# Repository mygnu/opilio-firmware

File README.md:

# opilio-firmware

Firmware for STM32F103C8 based custom board for PC water-cooling project.

Counterparts: 
- Linux TUI app can be found [here](https://github.com/mygnu/opilio)
- PCB Files [here](https://github.com/mygnu/opilio-pcb)

## Flashing an opilio board
- install rust from [rustup](https://rustup.rs)
- `cargo install probe-run cargo-flash flip-link`
- `git clone https://github.com/mygnu/opilio`
- `git clone https://github.com/mygnu/opilio-firmware`
- `cd opilio-firmware && cargo flash --chip STM32F103C8 --release`

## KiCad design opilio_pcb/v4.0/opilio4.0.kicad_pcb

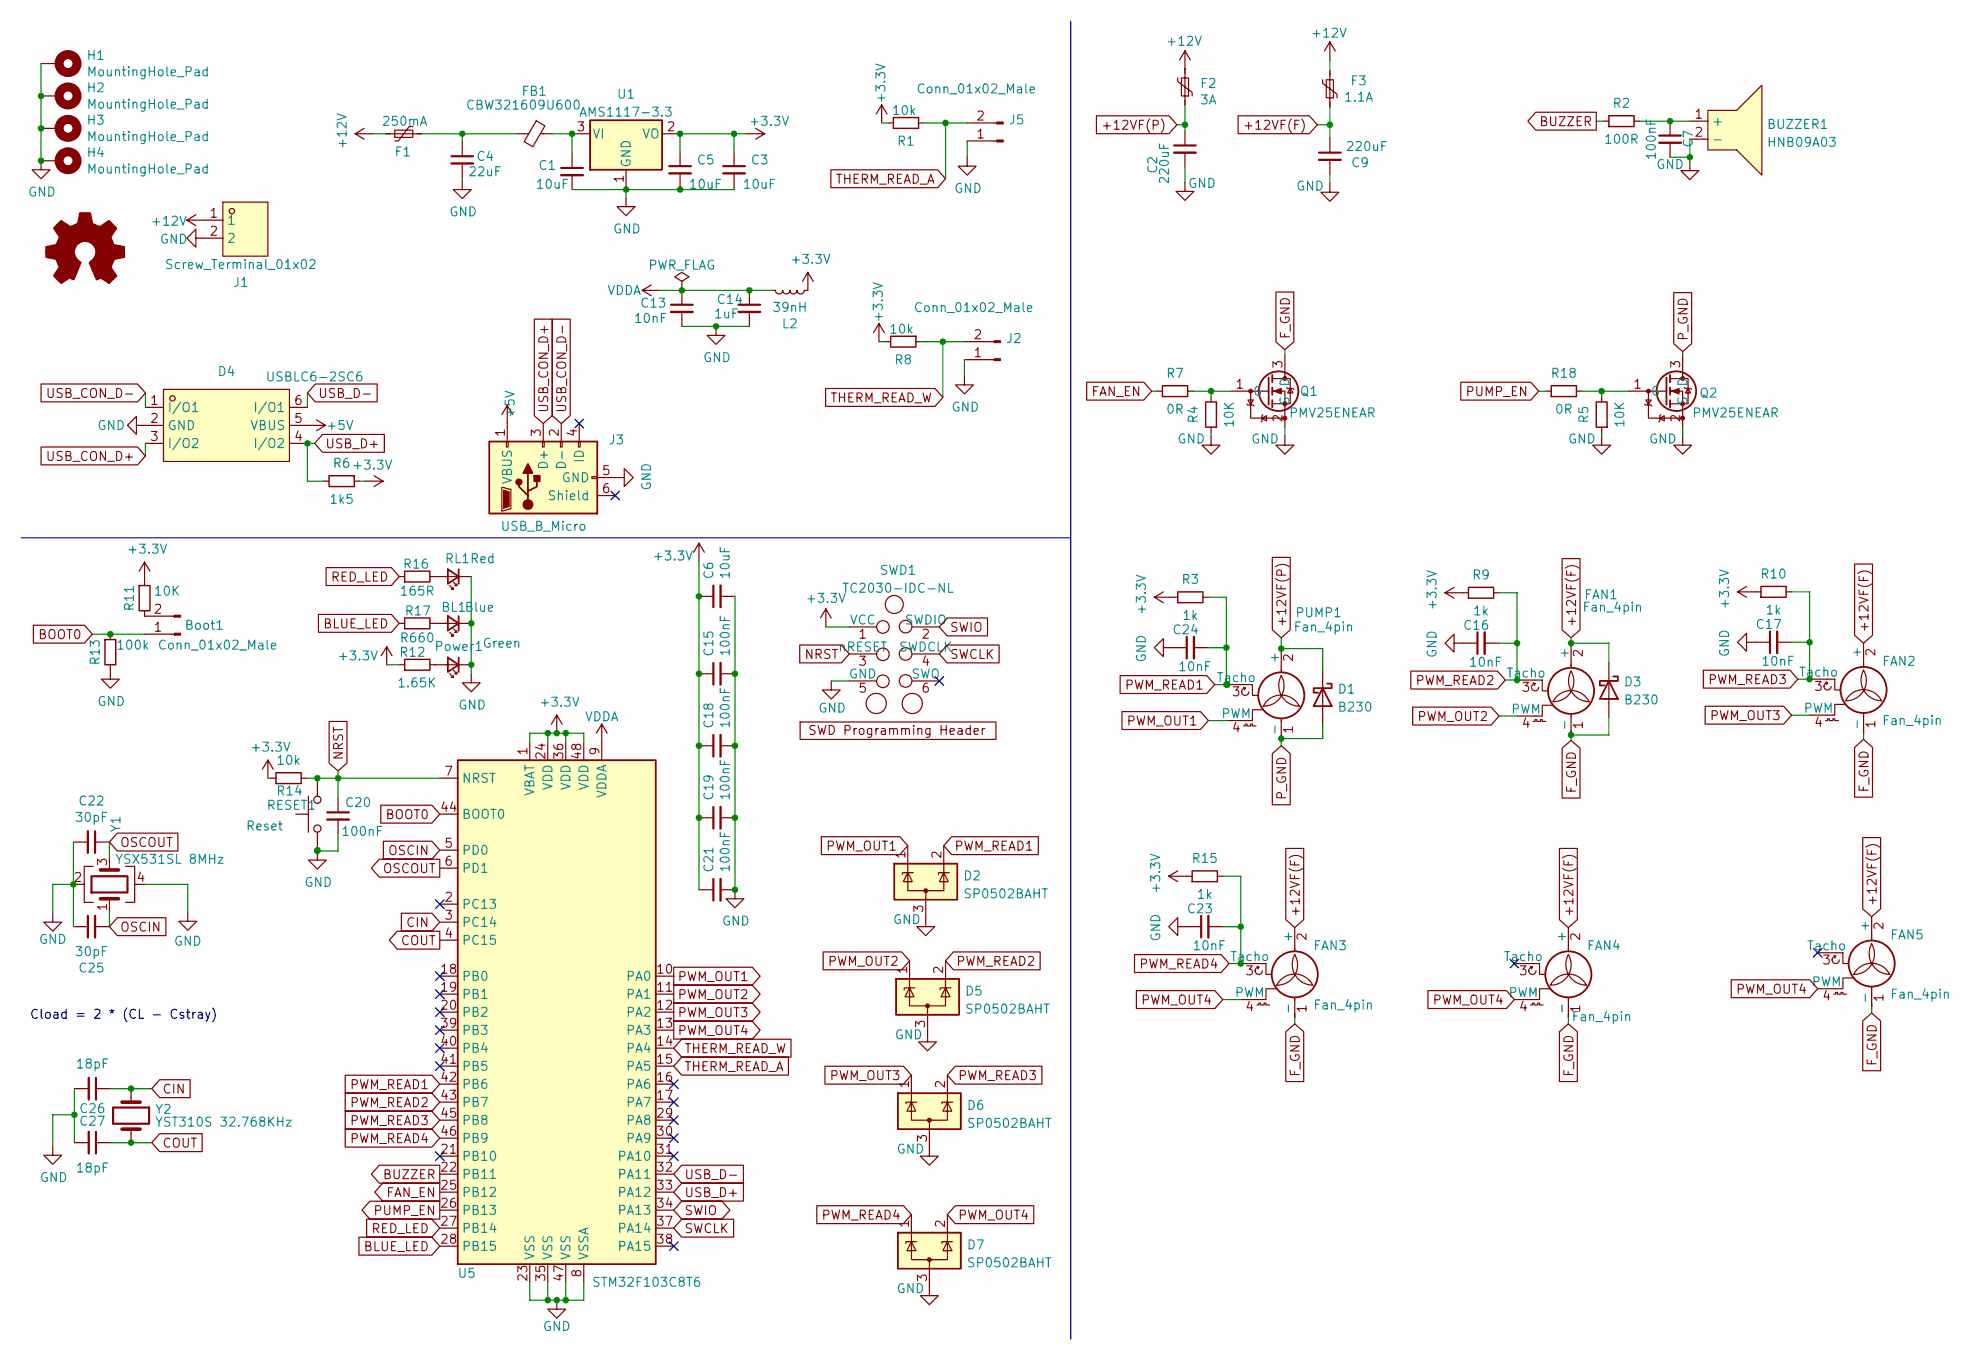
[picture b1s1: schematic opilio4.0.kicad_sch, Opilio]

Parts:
BL1: Blue; LED_0603_1608Metric_Pad1.05x0.95mm_HandSolder
BUZZER1: HNB09A03; BUZ-TH_BD9.0-P5.00-D0.6-FD; LCSC Part C96102
Boot1: Conn_01x02_Male; PinHeader_1x02_P2.54mm_Vertical
C1, C3, C5, C6: 10uF; C_0603_1608Metric_Pad1.08x0.95mm_HandSolder
C2, C9: 220uF; CP_Elec_6.3x7.7
C4: 22uF; C_1206_3216Metric_Pad1.33x1.80mm_HandSolder
C7, C15, C18, C19, C20, C21: 100nF; C_0603_1608Metric_Pad1.08x0.95mm_HandSolder
C13, C16, C17, C23, C24: 10nF; C_0603_1608Metric_Pad1.08x0.95mm_HandSolder
C14: 1uF; C_0603_1608Metric_Pad1.08x0.95mm_HandSolder
C22, C25: 30pF; C_0603_1608Metric_Pad1.08x0.95mm_HandSolder
C26, C27: 18pF; C_0603_1608Metric_Pad1.08x0.95mm_HandSolder
D1, D3: B230; D_SMB
D2, D5, D6, D7: SP0502BAHT; SOT-23
D4: USBLC6-2SC6; SOT-666-6_L1.6-W1.2-P0.50-LS1.6-BL; LCSC Part C2827693
F1: 250mA; Fuse_1206_3216Metric_Pad1.42x1.75mm_HandSolder
F2: 3A; Fuse_1812_4532Metric_Pad1.30x3.40mm_HandSolder
F3: 1.1A; Fuse_1206_3216Metric_Pad1.42x1.75mm_HandSolder
FAN1, FAN2, FAN3, FAN4, FAN5: Fan_4pin; FanPinHeader_1x04_P2.54mm_Vertical_no_hole
FB1: CBW321609U600; C_1206_3216Metric_Pad1.33x1.80mm_HandSolder
H1, H2, H3, H4: MountingHole_Pad; MountingHole_3mm_Pad_Via
J1: Screw_Terminal_01x02; CONN-TH_2P-P2.54_JL300-50002U01; LCSC Part C387831
J2, J5: Conn_01x02_Male; PinHeader_1x02_P2.54mm_Vertical
J3: USB_B_Micro; USB_Micro-B_Wuerth_629105150521_narrow_holes
L2: 39nH; L_0805_2012Metric_Pad1.05x1.20mm_HandSolder
LOGO1: Logo_Open_Hardware_Small; OSHW-Logo2_9.8x8mm_SilkScreen
PUMP1: Fan_4pin; FanPinHeader_1x04_P2.54mm_Vertical_no_hole
Power1: Green; LED_0603_1608Metric_Pad1.05x0.95mm_HandSolder
Q1, Q2: PMV25ENEAR; SOT-23_L2.9-W1.3-P1.90-LS2.4-BR; LCSC Part C458158
R1, R8, R14: 10k; R_0603_1608Metric_Pad0.98x0.95mm_HandSolder
R2: 100R; R_0603_1608Metric_Pad0.98x0.95mm_HandSolder
R3, R9, R10, R15: 1k; R_0603_1608Metric_Pad0.98x0.95mm_HandSolder
R4, R5, R11: 10K; R_0603_1608Metric_Pad0.98x0.95mm_HandSolder
R6: 1k5; R_0603_1608Metric_Pad0.98x0.95mm_HandSolder
R7, R18: 0R; R_0603_1608Metric_Pad0.98x0.95mm_HandSolder
R12: 1.65K; R_0603_1608Metric_Pad0.98x0.95mm_HandSolder
R13: 100k; R_0603_1608Metric_Pad0.98x0.95mm_HandSolder
R16: 165R; R_0603_1608Metric_Pad0.98x0.95mm_HandSolder
R17: R660; R_0603_1608Metric_Pad0.98x0.95mm_HandSolder
RESET1: Reset; SW-SMD_L6.0-W3.3-LS8.0
RL1: Red; LED_0603_1608Metric_Pad1.05x0.95mm_HandSolder
SWD1: TC2030-IDC-NL_SWD; Tag-Connect_TC2030-IDC-NL_2x03_P1.27mm_Vertical
U1: AMS1117-3.3; SOT-223-3_TabPin2
U5: STM32F103C8T6; LQFP-48_7x7mm_P0.5mm
Y1: YSX531SL 8MHz; Crystal_SMD_3225-4Pin_3.2x2.5mm
Y2: YST310S 32.768KHz; Crystal_SMD_3215-2Pin_3.2x1.5mm

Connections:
+3.3V: C3.1, C5.1, C6.1, C15.1, C18.1, C19.1, C21.1, L2.1, R1.2, R3.1, R6.1, R8.2, R9.1, R10.1, R11.1, R12.1, R14.1, R15.1, SWD1.1 (VCC), U1.2 (VO), U5.1 (VBAT), U5.24 (VDD), U5.36 (VDD), U5.48 (VDD)
+5V: D4.5 (VBUS), J3.1 (VBUS)
+12V: F1.1, F2.2, F3.2, J1.1
+12VF(F): C9.1, D3.1 (K), F3.1, FAN1.2 (+), FAN2.2 (+), FAN3.2 (+), FAN4.2 (+), FAN5.2 (+)
+12VF(P): C2.1, D1.1 (K), F2.1, PUMP1.2 (+)
BLUE_LED: R17.1, U5.28 (PB15)
BOOT0: Boot1.1, R13.1, U5.44 (BOOT0)
BUZZER: R2.1, U5.22 (PB11)
CIN: C26.1, U5.3 (PC14), Y2.1
COUT: C27.1, U5.4 (PC15), Y2.2
FAN_EN: R7.1, U5.25 (PB12)
F_GND: D3.2 (A), FAN1.1 (-), FAN2.1 (-), FAN3.1 (-), FAN4.1 (-), FAN5.1 (-), Q1.3 (D)
GND: BL1.1 (K), BUZZER1.2 (-), C1.2, C2.2, C3.2, C4.2, C5.2, C6.2, C7.2, C9.2, C13.2, C14.2, C15.2, C16.1, C17.1, C18.2, C19.2, C20.2, C21.2, C22.2, C23.1, C24.1, C25.1, C26.2, C27.2, D2.3 (A), D4.2 (GND), D5.3 (A), D6.3 (A), D7.3 (A), H1.1, H2.1, H3.1, H4.1, J1.2, J2.1, J3.5 (GND), J5.1, Power1.1 (K), Q1.2 (S), Q2.2 (S), R4.1, R5.1, R13.2, RESET1.1, RL1.1 (K), SWD1.5 (GND), U1.1 (GND), U5.8 (VSSA), U5.23 (VSS), U5.35 (VSS), U5.47 (VSS), Y1.2, Y1.4
NRST: C20.1, R14.2, RESET1.2, SWD1.3 (nRESET), U5.7 (NRST)
unnamed: BL1.2 (A), R17.2
unnamed: BUZZER1.1 (+), C7.1, R2.2
unnamed: Boot1.2, R11.2
unnamed: C1.1, FB1.1, U1.3 (VI)
unnamed: C4.1, F1.2, FB1.2
unnamed: Power1.2 (A), R12.2
unnamed: Q1.1 (G), R4.2, R7.2
unnamed: Q2.1 (G), R5.2, R18.2
unnamed: R16.2, RL1.2 (A)
OSCIN: C25.2, U5.5 (PD0), Y1.1
OSCOUT: C22.1, U5.6 (PD1), Y1.3
PUMP_EN: R18.1, U5.26 (PB13)
PWM_OUT1: D2.1 (K), PUMP1.4 (PWM), U5.10 (PA0)
PWM_OUT2: D5.1 (K), FAN1.4 (PWM), U5.11 (PA1)
PWM_OUT3: D6.1 (K), FAN2.4 (PWM), U5.12 (PA2)
PWM_OUT4: D7.2 (K), FAN3.4 (PWM), FAN4.4 (PWM), FAN5.4 (PWM), U5.13 (PA3)
PWM_READ1: C24.2, D2.2 (K), PUMP1.3 (Tacho), R3.2, U5.42 (PB6)
PWM_READ2: C16.2, D5.2 (K), FAN1.3 (Tacho), R9.2, U5.43 (PB7)
PWM_READ3: C17.2, D6.2 (K), FAN2.3 (Tacho), R10.2, U5.45 (PB8)
PWM_READ4: C23.2, D7.1 (K), FAN3.3 (Tacho), R15.2, U5.46 (PB9)
P_GND: D1.2 (A), PUMP1.1 (-), Q2.3 (D)
RED_LED: R16.1, U5.27 (PB14)
SWCLK: SWD1.4 (SWDCLK), U5.37 (PA14)
SWIO: SWD1.2 (SWDIO), U5.34 (PA13)
THERM_READ_A: J5.2, R1.1, U5.15 (PA5)
THERM_READ_W: J2.2, R8.1, U5.14 (PA4)
USB_CON_D+: D4.3 (I/O2), J3.3 (D+)
USB_CON_D-: D4.1 (I/O1), J3.2 (D-)
USB_D+: D4.4 (I/O2), R6.2, U5.33 (PA12)
USB_D-: D4.6 (I/O1), U5.32 (PA11)
VDDA: C13.1, C14.1, L2.2, U5.9 (VDDA)

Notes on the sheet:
Cload = 2 * (CL - Cstray)

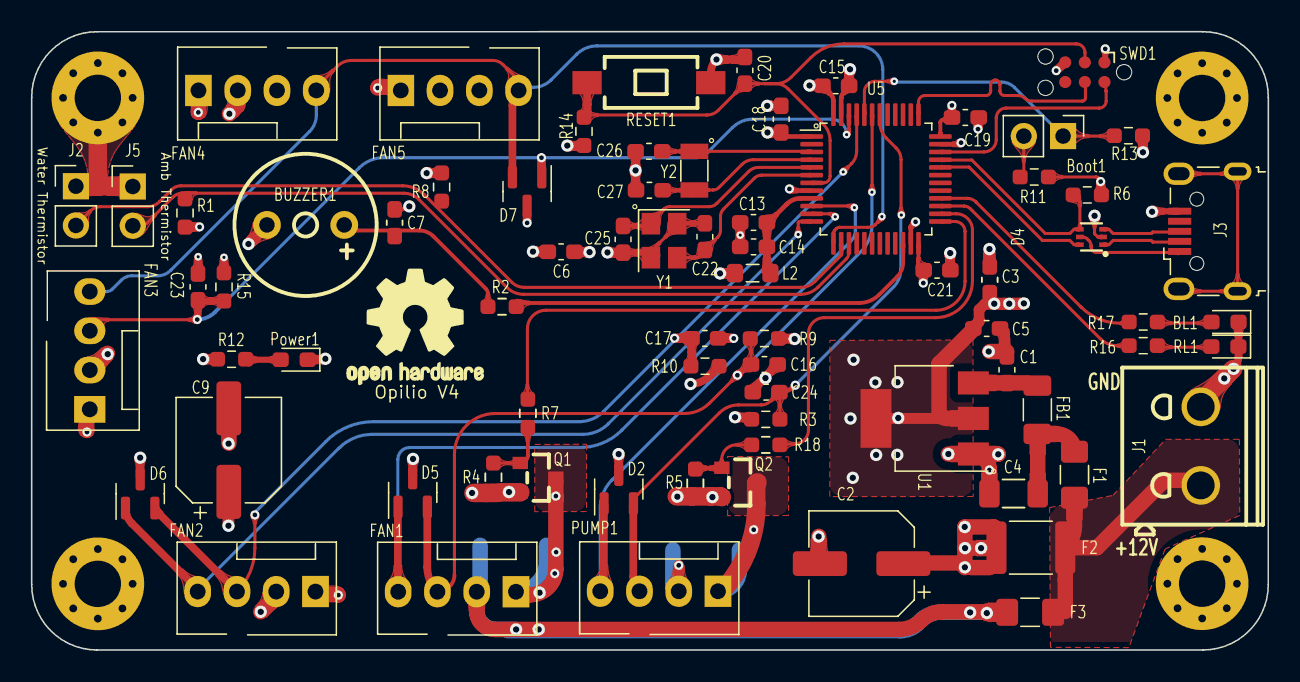
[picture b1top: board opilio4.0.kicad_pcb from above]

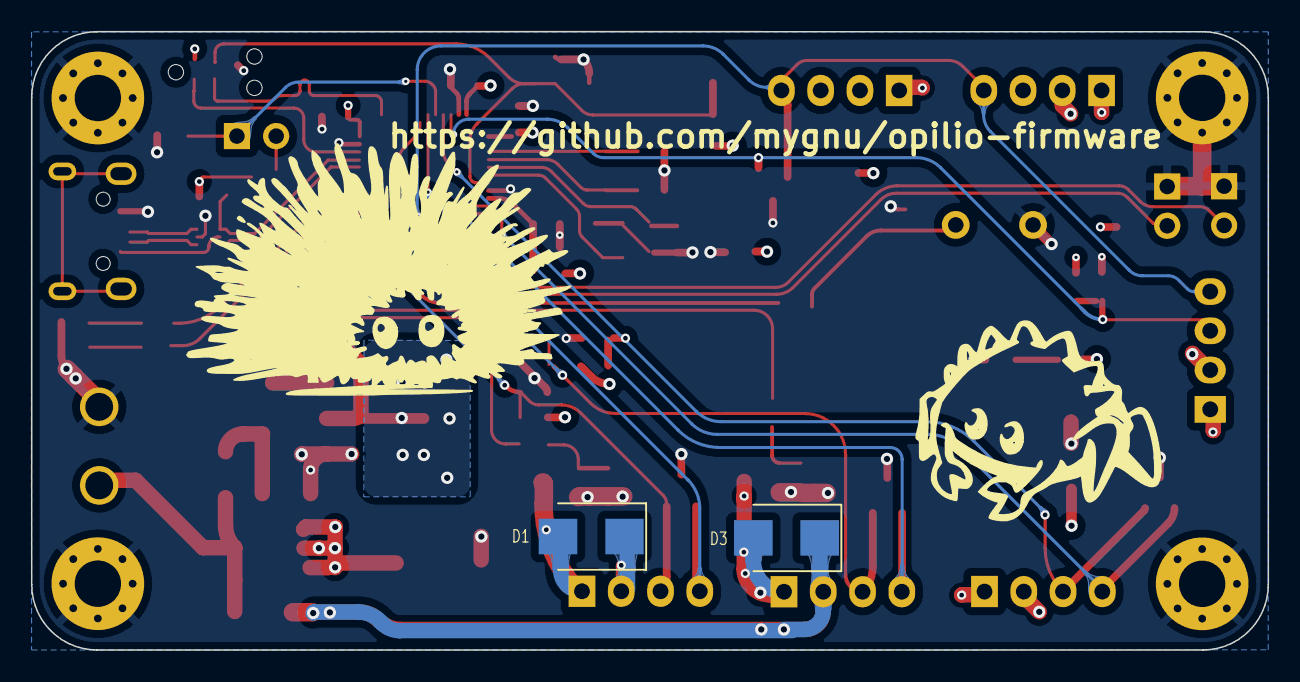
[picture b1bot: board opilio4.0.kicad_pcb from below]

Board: 4 copper layers, 80.0 x 40.0 mm, 81 parts (2 on the bottom side), 45 nets.

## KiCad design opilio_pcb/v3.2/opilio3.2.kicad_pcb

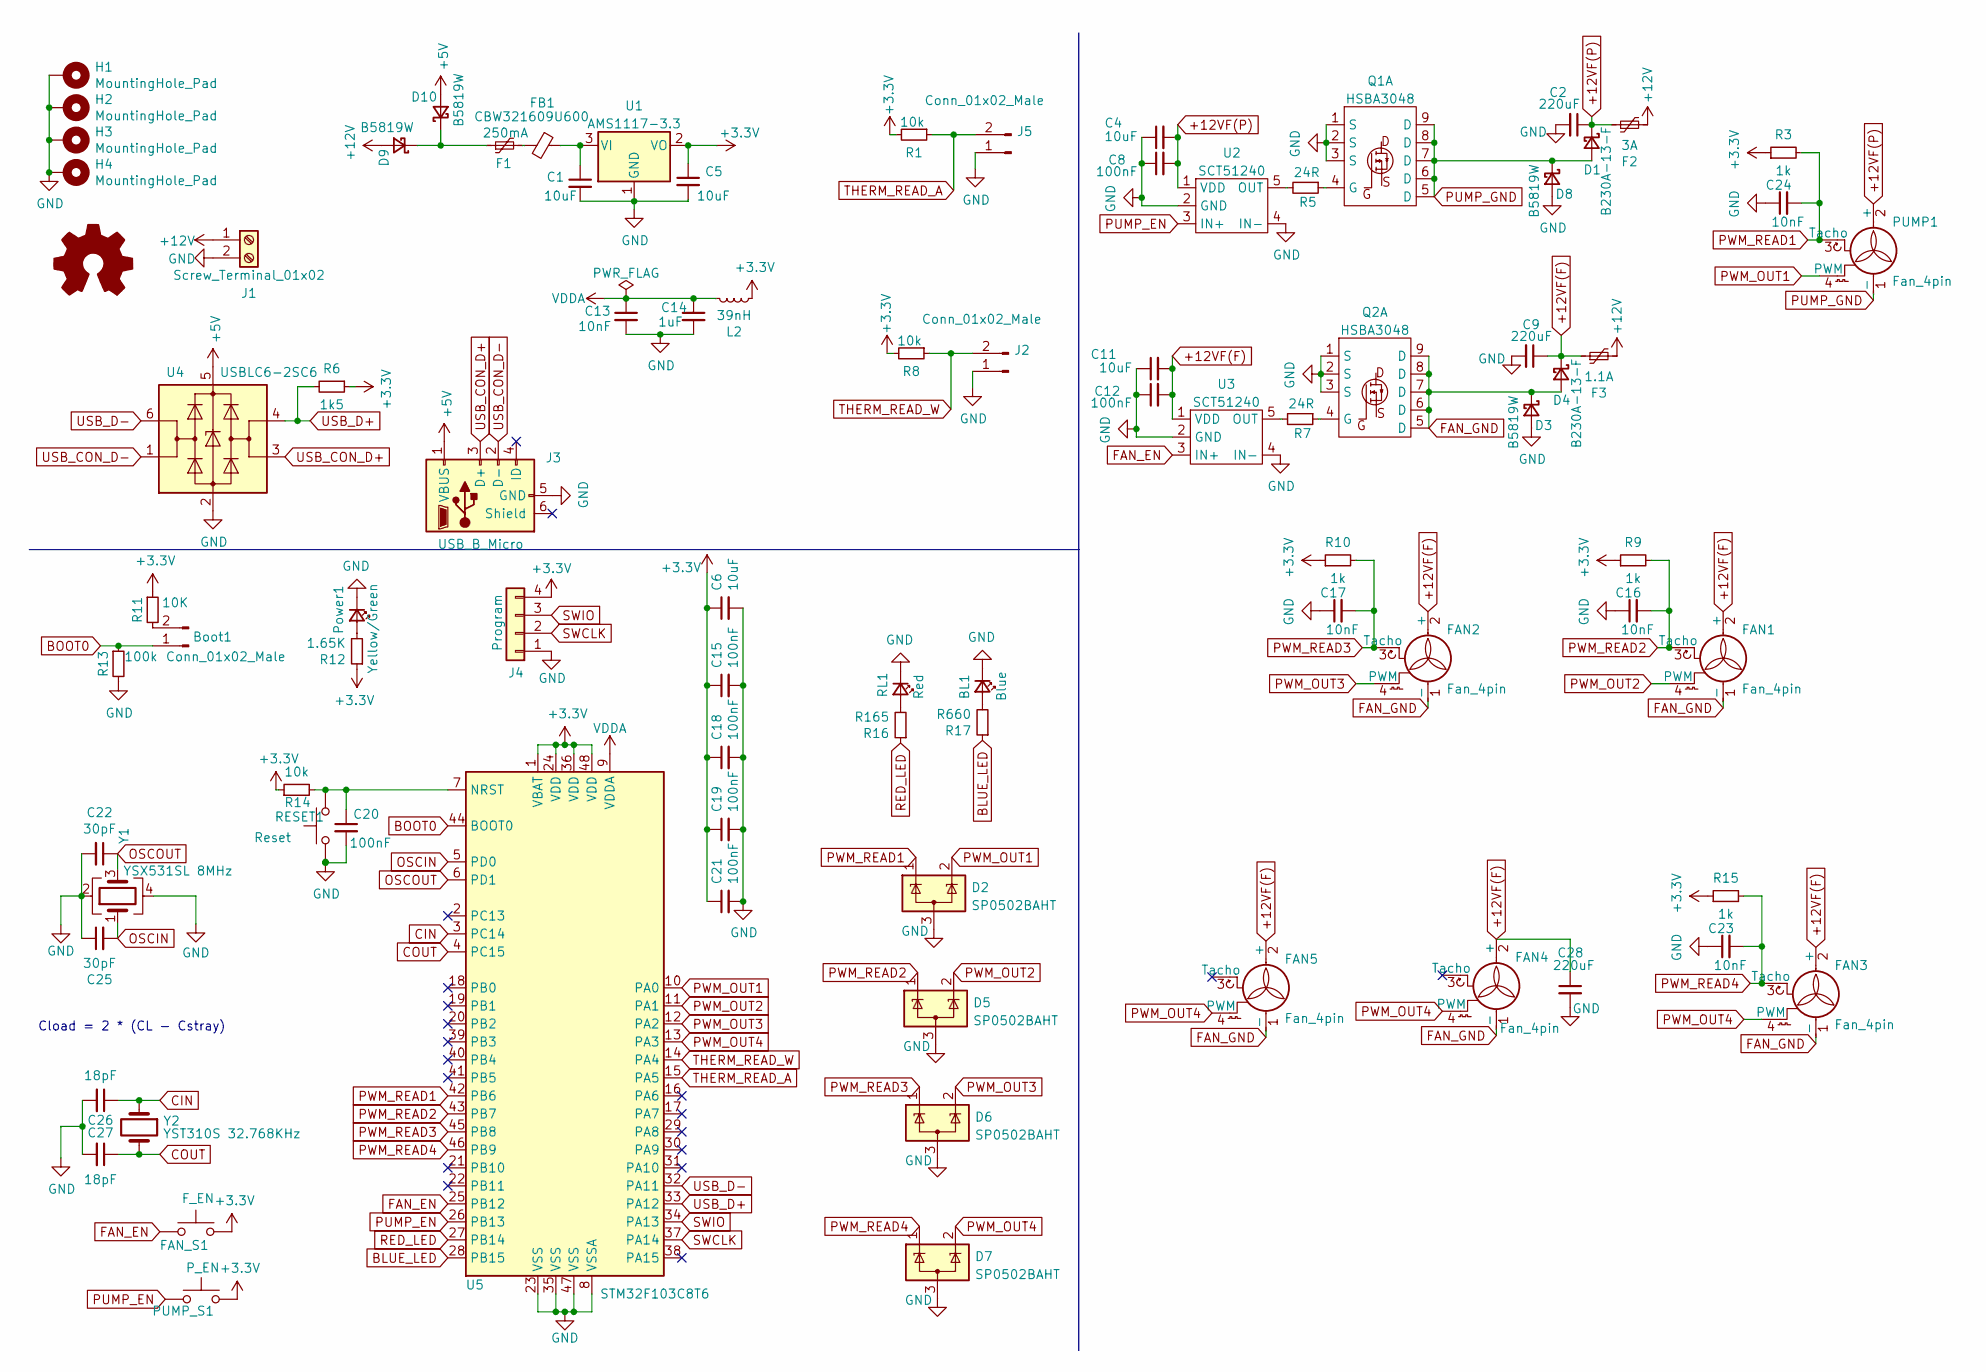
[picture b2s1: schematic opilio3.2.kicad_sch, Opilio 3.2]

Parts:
BL1: Blue; LED_0603_1608Metric_Pad1.05x0.95mm_HandSolder
Boot1: Conn_01x02_Male; PinHeader_1x02_P2.54mm_Vertical
C1, C4, C5, C6, C11: 10uF; C_0603_1608Metric_Pad1.08x0.95mm_HandSolder
C2, C9, C28: 220uF; CP_Elec_6.3x7.7
C8, C12, C15, C18, C19, C20, C21: 100nF; C_0603_1608Metric_Pad1.08x0.95mm_HandSolder
C13, C16, C17, C23, C24: 10nF; C_0603_1608Metric_Pad1.08x0.95mm_HandSolder
C14: 1uF; C_0603_1608Metric_Pad1.08x0.95mm_HandSolder
C22, C25: 30pF; C_0603_1608Metric_Pad1.08x0.95mm_HandSolder
C26, C27: 18pF; C_0603_1608Metric_Pad1.08x0.95mm_HandSolder
D1, D4: B230A-13-F; D_SMA
D2, D5, D6, D7: SP0502BAHT; SOT-23
D3, D8, D9, D10: B5819W; D_SOD-123
F1: 250mA; Fuse_1206_3216Metric_Pad1.42x1.75mm_HandSolder
F2: 3A; Fuse_1812_4532Metric_Pad1.30x3.40mm_HandSolder
F3: 1.1A; Fuse_1206_3216Metric_Pad1.42x1.75mm_HandSolder
FAN1, FAN2, FAN3, FAN4, FAN5: Fan_4pin; FanPinHeader_1x04_P2.54mm_Vertical_no_hole
FAN_S1: F_EN; SW-SMD_L6.0-W3.3-LS8.0
FB1: CBW321609U600; C_1206_3216Metric_Pad1.33x1.80mm_HandSolder
H1, H2, H3, H4: MountingHole_Pad; MountingHole_3mm_Pad_Via
J1: Screw_Terminal_01x02; TerminalBlock_bornier-2_P5.08mm
J2, J5: Conn_01x02_Male; PinHeader_1x02_P2.54mm_Vertical
J3: USB_B_Micro; USB_Micro-B_Wuerth_629105150521_narrow_holes
J4: Program; PinHeader_1x04_P2.54mm_Vertical
L2: 39nH; L_0805_2012Metric_Pad1.05x1.20mm_HandSolder
LOGO1: Logo_Open_Hardware_Small; OSHW-Logo2_9.8x8mm_SilkScreen
PUMP1: Fan_4pin; FanPinHeader_1x04_P2.54mm_Vertical_no_hole
PUMP_S1: P_EN; SW-SMD_L6.0-W3.3-LS8.0
Power1: Yellow/Green; LED_0603_1608Metric_Pad1.05x0.95mm_HandSolder
Q1, Q2: HSBA3048; PDFN-8_L5.6-W5.2-P1.27-LS6.1-BL
R1, R8, R14: 10k; R_0603_1608Metric_Pad0.98x0.95mm_HandSolder
R3, R9, R10, R15: 1k; R_0603_1608Metric_Pad0.98x0.95mm_HandSolder
R5, R7: 24R; R_0603_1608Metric_Pad0.98x0.95mm_HandSolder
R6: 1k5; R_0603_1608Metric_Pad0.98x0.95mm_HandSolder
R11: 10K; R_0603_1608Metric_Pad0.98x0.95mm_HandSolder
R12: 1.65K; R_0603_1608Metric_Pad0.98x0.95mm_HandSolder
R13: 100k; R_0603_1608Metric_Pad0.98x0.95mm_HandSolder
R16: R165; R_0603_1608Metric_Pad0.98x0.95mm_HandSolder
R17: R660; R_0603_1608Metric_Pad0.98x0.95mm_HandSolder
RESET1: Reset; SW-SMD_L6.0-W3.3-LS8.0
RL1: Red; LED_0603_1608Metric_Pad1.05x0.95mm_HandSolder
U1: AMS1117-3.3; SOT-223-3_TabPin2
U2, U3: SCT51240; SOT-23-5_HandSoldering
U4: USBLC6-2SC6; SOT-23-6
U5: STM32F103C8T6; LQFP-48_7x7mm_P0.5mm
Y1: YSX531SL 8MHz; Crystal_SMD_3225-4Pin_3.2x2.5mm
Y2: YST310S 32.768KHz; Crystal_SMD_3215-2Pin_3.2x1.5mm

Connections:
+3.3V: C5.1, C6.1, C15.1, C18.1, C19.1, C21.1, FAN_S1.2, J4.4, L2.1, PUMP_S1.2, R1.2, R3.1, R6.1, R8.2, R9.1, R10.1, R11.1, R12.1, R14.1, R15.1, U1.2 (VO), U5.1 (VBAT), U5.24 (VDD), U5.36 (VDD), U5.48 (VDD)
+5V: D10.2 (A), J3.1 (VBUS), U4.5 (VBUS)
+12V: D9.2 (A), F2.2, F3.2, J1.1
+12VF(F): C9.1, C11.2, C12.2, C28.1, D4.1 (K), F3.1, FAN1.2 (+), FAN2.2 (+), FAN3.2 (+), FAN4.2 (+), FAN5.2 (+), U3.1 (VDD)
+12VF(P): C2.1, C4.2, C8.2, D1.1 (K), F2.1, PUMP1.2 (+), U2.1 (VDD)
BLUE_LED: R17.1, U5.28 (PB15)
BOOT0: Boot1.1, R13.1, U5.44 (BOOT0)
CIN: C26.1, U5.3 (PC14), Y2.1
COUT: C27.1, U5.4 (PC15), Y2.2
FAN_EN: FAN_S1.1, U3.3 (IN+), U5.25 (PB12)
FAN_GND: D3.1 (K), D4.2 (A), FAN1.1 (-), FAN2.1 (-), FAN3.1 (-), FAN4.1 (-), FAN5.1 (-), Q2.5 (D), Q2.6 (D), Q2.7 (D), Q2.8 (D), Q2.9 (D)
GND: BL1.1 (K), C1.2, C2.2, C4.1, C5.2, C6.2, C8.1, C9.2, C11.1, C12.1, C13.2, C14.2, C15.2, C16.1, C17.1, C18.2, C19.2, C20.2, C21.2, C22.2, C23.1, C24.1, C25.1, C26.2, C27.2, C28.2, D2.3 (A), D3.2 (A), D5.3 (A), D6.3 (A), D7.3 (A), D8.2 (A), H1.1, H2.1, H3.1, H4.1, J1.2, J2.1, J3.5 (GND), J4.1, J5.1, Power1.1 (K), Q1.1 (S), Q1.2 (S), Q1.3 (S), Q2.1 (S), Q2.2 (S), Q2.3 (S), R13.2, RESET1.1, RL1.1 (K), U1.1 (GND), U2.2 (GND), U2.4 (IN-), U3.2 (GND), U3.4 (IN-), U4.2 (GND), U5.8 (VSSA), U5.23 (VSS), U5.35 (VSS), U5.47 (VSS), Y1.2, Y1.4
unnamed: BL1.2 (A), R17.2
unnamed: Boot1.2, R11.2
unnamed: C1.1, FB1.1, U1.3 (VI)
unnamed: C20.1, R14.2, RESET1.2, U5.7 (NRST)
unnamed: D9.1 (K), D10.1 (K), F1.1
unnamed: F1.2, FB1.2
unnamed: Power1.2 (A), R12.2
unnamed: Q1.4 (G), R5.1
unnamed: Q2.4 (G), R7.1
unnamed: R5.2, U2.5 (OUT)
unnamed: R7.2, U3.5 (OUT)
unnamed: R16.2, RL1.2 (A)
OSCIN: C25.2, U5.5 (PD0), Y1.1
OSCOUT: C22.1, U5.6 (PD1), Y1.3
PUMP_EN: PUMP_S1.1, U2.3 (IN+), U5.26 (PB13)
PUMP_GND: D1.2 (A), D8.1 (K), PUMP1.1 (-), Q1.5 (D), Q1.6 (D), Q1.7 (D), Q1.8 (D), Q1.9 (D)
PWM_OUT1: D2.2 (K), PUMP1.4 (PWM), U5.10 (PA0)
PWM_OUT2: D5.2 (K), FAN1.4 (PWM), U5.11 (PA1)
PWM_OUT3: D6.2 (K), FAN2.4 (PWM), U5.12 (PA2)
PWM_OUT4: D7.2 (K), FAN3.4 (PWM), FAN4.4 (PWM), FAN5.4 (PWM), U5.13 (PA3)
PWM_READ1: C24.2, D2.1 (K), PUMP1.3 (Tacho), R3.2, U5.42 (PB6)
PWM_READ2: C16.2, D5.1 (K), FAN1.3 (Tacho), R9.2, U5.43 (PB7)
PWM_READ3: C17.2, D6.1 (K), FAN2.3 (Tacho), R10.2, U5.45 (PB8)
PWM_READ4: C23.2, D7.1 (K), FAN3.3 (Tacho), R15.2, U5.46 (PB9)
RED_LED: R16.1, U5.27 (PB14)
SWCLK: J4.2, U5.37 (PA14)
SWIO: J4.3, U5.34 (PA13)
THERM_READ_A: J5.2, R1.1, U5.15 (PA5)
THERM_READ_W: J2.2, R8.1, U5.14 (PA4)
USB_CON_D+: J3.3 (D+), U4.3 (I/O2)
USB_CON_D-: J3.2 (D-), U4.1 (I/O1)
USB_D+: R6.2, U4.4 (I/O2), U5.33 (PA12)
USB_D-: U4.6 (I/O1), U5.32 (PA11)
VDDA: C13.1, C14.1, L2.2, U5.9 (VDDA)

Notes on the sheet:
Cload = 2 * (CL - Cstray)

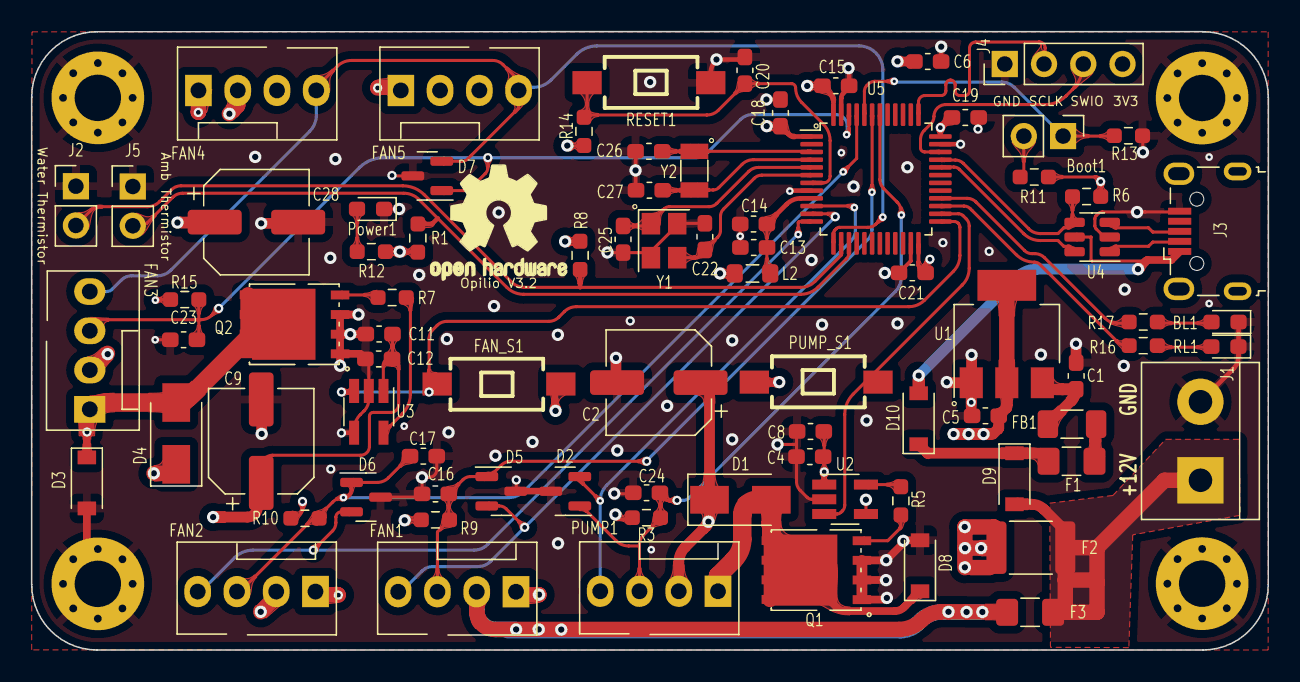
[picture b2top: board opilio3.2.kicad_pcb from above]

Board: 4 copper layers, 80.0 x 40.0 mm, 87 parts (0 on the bottom side), 46 nets.

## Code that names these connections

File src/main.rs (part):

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        // Pull the D+ pin down to send a RESET condition to the USB bus.
        // This forced reset is needed only for development, without it host
        // will not reset your device when you upload new firmware.
        let mut usb_dp = gpioa.pa12.into_push_pull_output(&mut gpioa.crh);
        usb_dp.set_low();
        delay(clocks.sysclk().raw() / 10);

        let usb_dm = gpioa.pa11;
        let usb_dp = usb_dp.into_floating_input(&mut gpioa.crh);

        let usb = Peripheral {
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        // Initialize the monotonic (SysTick rate is 48 MHz)
        let mono = Systick::new(cx.core.SYST, 48_000_000);

        // Configure pa4 as an analog input
        let ambient_thermistor = gpioa.pa4.into_analog(&mut gpioa.crl);
        let coolant_thermistor = gpioa.pa5.into_analog(&mut gpioa.crl);
        let coolant_out_thermistor = gpioa.pa6.into_analog(&mut gpioa.crl);

        let pins_a0_a3 = (
            gpioa.pa0.into_alternate_push_pull(&mut gpioa.crl),
            gpioa.pa1.into_alternate_push_pull(&mut gpioa.crl),
            gpioa.pa2.into_alternate_push_pull(&mut gpioa.crl),
            gpioa.pa3.into_alternate_push_pull(&mut gpioa.crl),
        );
        let pwm_timer2: PwmTimer2 = device.TIM2.pwm_hz::<Tim2NoRemap, _, _>(
            pins_a0_a3,
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            &clocks,
        );

        let buzzer = gpiob.pb11.into_push_pull_output(&mut gpiob.crh);
        let pump_power = gpiob.pb12.into_push_pull_output(&mut gpiob.crh);
        let fan_power = gpiob.pb13.into_push_pull_output(&mut gpiob.crh);
        let red_led = gpiob.pb14.into_push_pull_output(&mut gpiob.crh);
        let green_led = gpioa.pa8.into_push_pull_output(&mut gpioa.crh);
        let blue_led = gpiob.pb15.into_push_pull_output(&mut gpiob.crh);
        let mut led = RgbLed::new(red_led, green_led, blue_led);
        led.exclusive_on(opilio_firmware::controller::Led::GREEN);

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            pwm_timer2, pump_power, fan_power, buzzer, temps, led,
        );

        timer4_input_setup(gpiob.pb6, gpiob.pb7, gpiob.pb8, gpiob.pb9);

        let tacho = TachoReader::default();

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
mod timer_setup {
    use stm32f1xx_hal::{
        gpio::{Floating, Input, PB6, PB7, PB8, PB9},
        pac::{Interrupt, RCC, TIM4},
        rcc::{Enable, Reset},
    };
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    /// setup timer (fake consumption of pins so we don't accidentally use them
    /// for other purposes)
    pub fn timer4_input_setup(
        _pb6: PB6<Input<Floating>>,
        _pb7: PB7<Input<Floating>>,
        _pb8: PB8<Input<Floating>>,
        _pb9: PB9<Input<Floating>>,
    ) {
        let tim = unsafe { &(*TIM4::ptr()) };

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            TIM4::reset(rcc);
        }

        // PB6, PB7, PB8, PB9
        // Disable capture on all 4 channels during setting
        // (for Channel X bit is CCXE)
        tim.ccer.modify(|_, w| {
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
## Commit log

2021-11-18 flash memory works
2021-11-18 still working
2021-11-18 timers updated fmt
2021-11-19 renames
2021-11-20 cleanup
2021-11-20 all peripherals working
2021-11-29 add missing file
2021-12-11 move all controls to the Controller
2022-01-12 before update
2022-01-16 before rtic
2022-01-31 rtic
2022-03-07 migrated to rtic
2022-03-13 set get save config
2022-05-16 before 307
2022-05-16 update hal
2022-06-21 opilio3
2022-06-23 wip usb serial
2022-06-24 rename
2022-06-24 using RTIC and separate carte for data (#1)
    some good comment
2022-06-25 Create LICENCE.md (#2)
2022-06-26 implement simple commands over usb serial
2022-06-27 Update LICENCE.md
    typo
2022-06-27 improved documentation
2022-06-27 improved documentation (#3)
2022-06-28 add renders and KiCad project files
2022-06-28 Add KiCad project files, and update readme (#4)
    * add renders and KiCad project files
2022-07-02 basic data fetch and charts
2022-07-02 improve usb serial communication (#5)
    * improved documentation
    * add renders and KiCad project files
    * basic data fetch and charts
2022-07-02 dependency update
2022-07-03 update device name
2022-07-03 Corrected a minor typo in README.md
2022-07-03 Corrected a minor typo in README.md (#6)
2022-07-04 refactor to updated shared lib
2022-07-04 stabalize temp reading by averaging
2022-07-05 move schematice tiny bit
2022-07-05 add power flag
2022-07-09 common
2022-07-10 save standby
2022-07-10 move duty calculation to config, prep for fan curve
2022-07-13 update pcb
2022-07-14 set led high if thermister value is too low
2022-07-14 deal with entire config
2022-07-15 add pcb v3.1
2022-07-15 moved opilio 3.1
2022-07-15 almost ready for v3.1
2022-07-16 add ambient temprature to stats
2022-07-16 uploading config works
2022-07-16 opt 3
2022-07-16 Board updated to v3.1 (#7)
    * refactor to updated shared lib
    * stabalize temp reading by averaging
    * stabalize temp reading by averaging
    * move schematice tiny bit
    * add power flag
    * common
2022-07-16 move renders out
2022-07-16 update render
2022-07-17 refactor
2022-07-17 refactor usb serial
2022-07-17 split and set each setting
2022-07-17 if liquid temp is cooler than the ambient, turn off fans
2022-07-19 butter handeling of stuff
2022-07-29 v3.2
2022-07-31 Pcb update to v3.2 (#9)
    * v3.2
    * cleanup
2022-07-31 pcb update
2022-07-31 pcb render
2022-07-31 add bom
2022-08-09 cargo update
2022-08-09 smaller mosfets
2022-08-15 v4 almost ready
2022-08-15 ordered
2022-08-15 render and deps update
2022-08-18 add tag-connect
2022-08-24 update schema files
2022-08-25 remove pcb files
2022-10-29 fix bug where memory not aligned
2022-12-01 use smart mode
2022-12-11 make flash and usb_handler local
2022-12-11 improve ui (#8)
    * move renders out
    * update render
    * refactor
    * refactor usb serial
    * split and set each setting
    * if liquid temp is cooler than the ambient, turn off fans
2022-12-14 added basic install instructions
2022-12-14 bump stm-hal
2023-01-05 cleanup and return version as serial number
2023-04-17 add reload command
2023-04-17 update firmware
2023-06-08 allow led and primary tepm input settings
2023-06-08 fix bug where config data not fully read
